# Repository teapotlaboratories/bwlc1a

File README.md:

# blwc1a
 Low-power Cellular GPS Tracker

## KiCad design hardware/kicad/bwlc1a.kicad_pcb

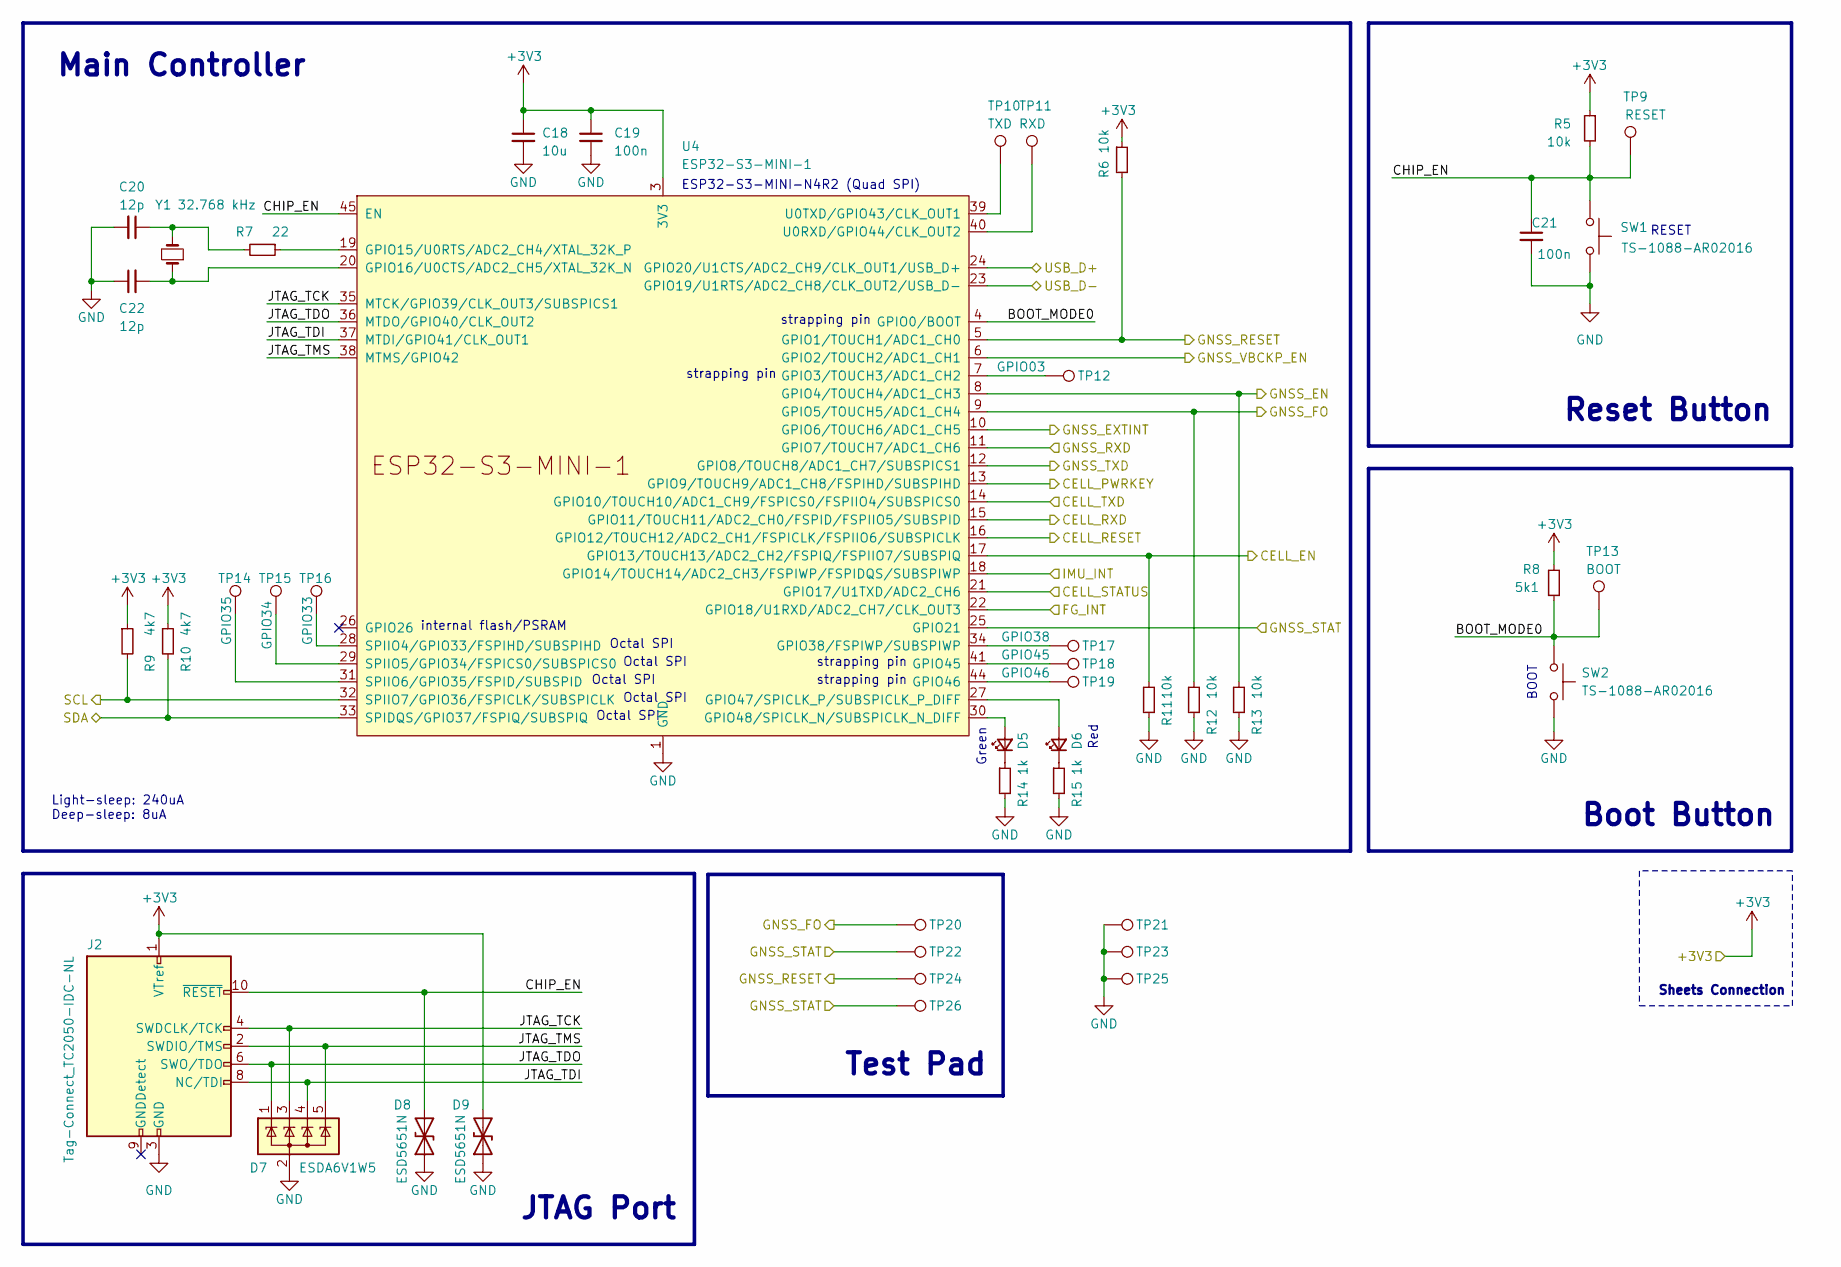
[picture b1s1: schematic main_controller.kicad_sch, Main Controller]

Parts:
C18: 10u; C_0603_1608Metric; Manufacturer Part Number CL10A106KP8NNNC
C19, C21: 100n; C_0402_1005Metric; Manufacturer Part Number CL05B104KO5NNNC
C20, C22: 12p; C_0402_1005Metric; Manufacturer Part Number 0402CG120J500NT
D5: LTST-C191KGKT; LED_0603_1608Metric; Manufacturer Part Number LTST-C191KGKT
D6: LTST-C191KRKT; LED_0603_1608Metric; Manufacturer Part Number LTST-C191KRKT
D7: ESDA6V1W5; SOT-353_SC-70-5; Manufacturer Part Number ESDA6V1W5
D8, D9: ESD5651N; D_SOD-882; Manufacturer Part Number ESD5651N
J2: Tag-Connect_TC2050-IDC-NL; Tag-Connect_TC2050-IDC-NL_2x05_P1.27mm_Vertical
R5, R6, R11, R12, R13: 10k; R_0402_1005Metric; Manufacturer Part Number 0402WGF1002TCE
R7: 22; R_0402_1005Metric; Manufacturer Part Number 0402WGF220JTCE
R8: 5k1; R_0402_1005Metric; Manufacturer Part Number 0402WGF5101TCE
R9, R10: 4k7; R_0402_1005Metric; Manufacturer Part Number 0402WGJ0472TCE
R14, R15: 1k; R_0402_1005Metric; Manufacturer Part Number 0402WGJ0102TCE
SW1, SW2: TS-1088-AR02016; SW-SMD_L3.9-W3.0-P4.45; Manufacturer Part Number TS-1088-AR02016
TP9: RESET; TestPoint_Pad_D1.0mm
TP10: TXD; TestPoint_Pad_D1.0mm
TP11: RXD; TestPoint_Pad_D1.0mm
TP12: GPIO03; TestPoint_Pad_D1.0mm
TP13: BOOT; TestPoint_Pad_D1.0mm
TP14: GPIO35; TestPoint_Pad_D1.0mm
TP15: GPIO34; TestPoint_Pad_D1.0mm
TP16: GPIO33; TestPoint_Pad_D1.0mm
TP17: GPIO38; TestPoint_Pad_D1.0mm
TP18: GPIO45; TestPoint_Pad_D1.0mm
TP19: GPIO46; TestPoint_Pad_D1.0mm
TP20, TP21, TP22, TP23, TP24, TP25, TP26: TestPoint_Pad_D1.0mm
U4: ESP32-S3-MINI-1; Manufacturer Part Number ESP32-S3-MINI-1-N4R2
Y1: 32.768 kHz; Crystal_SMD_3215-2Pin_3.2x1.5mm; Manufacturer Part Number Q13FC1350000400

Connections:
+3V3: C18.1, C19.1, D9.2 (A2), J2.1 (VTref), R5.1, R6.1, R8.2, R9.1, R10.1, U4.3 (3V3); also elsewhere on the board
/Cellular/CELL_PWRKEY: U4.13 (GPIO9/TOUCH9/ADC1_CH8/FSPIHD/SUBSPIHD); also elsewhere on the board
/Cellular/CELL_RESET: U4.16 (GPIO12/TOUCH12/ADC2_CH1/FSPICLK/FSPIIO6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); also elsewhere on the board
/Cellular/CELL_RXD: U4.15 (GPIO11/TOUCH11/ADC2_CH0/FSPID/FSPIIO5/S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); also elsewhere on the board
/Cellular/CELL_STATUS: U4.21 (GPIO17/U1TXD/ADC2_CH6); also elsewhere on the board
/Cellular/CELL_TXD: U4.14 (GPIO10/TOUCH10/ADC1_CH9/FSPICS0/FSPIIO4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); also elsewhere on the board
/GNSS/GNSS_EXTINT: U4.10 (GPIO6/TOUCH6/ADC1_CH5); also elsewhere on the board
/GNSS/GNSS_FO: R12.2, TP20.1, U4.9 (GPIO5/TOUCH5/ADC1_CH4); also elsewhere on the board
/GNSS/GNSS_RESET: R6.2, TP24.1, U4.5 (GPIO1/TOUCH1/ADC1_CH0); also elsewhere on the board
/GNSS/GNSS_RXD: U4.11 (GPIO7/TOUCH7/ADC1_CH6); also elsewhere on the board
/GNSS/GNSS_STAT: TP22.1, TP26.1, U4.25 (GPIO21); also elsewhere on the board
/GNSS/GNSS_TXD: U4.12 (GPIO8/TOUCH8/ADC1_CH7/SUBSPICS1); also elsewhere on the board
/Main Controller/BOOT_MODE0: R8.1, SW2.1, TP13.1, U4.4 (GPIO0/BOOT)
/Main Controller/CELL_EN: R11.2, U4.17 (GPIO13/TOUCH13/ADC2_CH2/FSPIQ/FSPIIO7/S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); also elsewhere on the board
/Main Controller/CHIP_EN: C21.1, D8.2 (A2), J2.10 (~RESET), R5.2, SW1.2, TP9.1, U4.45 (EN)
/Main Controller/FG_INT: U4.22 (GPIO18/U1RXD/ADC2_CH7/CLK_OUT3); also elsewhere on the board
/Main Controller/GNSS_EN: R13.2, U4.8 (GPIO4/TOUCH4/ADC1_CH3); also elsewhere on the board
/Main Controller/GNSS_VBCKP_EN: U4.6 (GPIO2/TOUCH2/ADC1_CH1); also elsewhere on the board
/Main Controller/IMU_INT: U4.18 (GPIO14/TOUCH14/ADC2_CH3/FSPIWP/FSPIDQS/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); also elsewhere on the board
/Main Controller/JTAG_TCK: D7.3 (K), J2.4 (SWDCLK/TCK), U4.35 (MTCK/GPIO39/CLK_OUT3/SUBSPICS1)
/Main Controller/JTAG_TDI: D7.4 (K), J2.8 (NC/TDI), U4.37 (MTDI/GPIO41/CLK_OUT1)
/Main Controller/JTAG_TDO: D7.1 (K), J2.6 (SWO/TDO), U4.36 (MTDO/GPIO40/CLK_OUT2)
/Main Controller/JTAG_TMS: D7.5 (K), J2.2 (SWDIO/TMS), U4.38 (MTMS/GPIO42)
/Main Controller/SCL: R9.2, U4.32 (SPIIO7/GPIO36/FSPICLK/SUBSPICLK); also elsewhere on the board
/Main Controller/SDA: R10.2, U4.33 (SPIDQS/GPIO37/FSPIQ/SUBSPIQ); also elsewhere on the board
/Main Controller/USB_D+: U4.24 (GPIO20/U1CTS/ADC2_CH9/CLK_OUT1/USB_D+); also elsewhere on the board
/Main Controller/USB_D-: U4.23 (GPIO19/U1RTS/ADC2_CH8/CLK_OUT2/USB_D-); also elsewhere on the board
GND: C18.2, C19.2, C20.2, C21.2, C22.1, D7.2 (A), D8.1 (A1), D9.1 (A1), J2.3 (GND), J2.5 (GND), R11.1, R12.1, R13.1, R14.2, R15.2, SW1.1, SW2.2, TP21.1, TP23.1, TP25.1, U4.1 (GND), U4.2 (GND), U4.42 (GND), U4.43 (GND), U4.46 (GND), U4.47 (GND), U4.48 (GND), U4.49 (GND), U4.50 (GND), U4.51 (GND), U4.52 (GND), U4.53 (GND), U4.54 (GND), U4.55 (GND), U4.56 (GND), U4.57 (GND), U4.58 (GND), U4.59 (GND), U4.60 (GND), U4.61 (GND), U4.62 (GND), U4.63 (GND), U4.64 (GND), U4.65 (GND); also elsewhere on the board
unnamed: C20.1, R7.2, Y1.2
unnamed: D5.2 (A), U4.30 (GPIO48/SPICLK_N/SUBSPICLK_N_DIFF)
unnamed: D5.1 (K), R14.1
unnamed: D6.2 (A), U4.27 (GPIO47/SPICLK_P/SUBSPICLK_P_DIFF)
unnamed: D6.1 (K), R15.1
unnamed: TP12.1, U4.7 (GPIO3/TOUCH3/ADC1_CH2)
unnamed: R7.1, U4.19 (GPIO15/U0RTS/ADC2_CH4/XTAL_32K_P)
unnamed: C22.2, U4.20 (GPIO16/U0CTS/ADC2_CH5/XTAL_32K_N), Y1.1
unnamed: TP17.1, U4.34 (GPIO38/FSPIWP/SUBSPIWP)
unnamed: TP18.1, U4.41 (GPIO45)
unnamed: TP19.1, U4.44 (GPIO46)
unnamed: TP16.1, U4.28 (SPIIO4/GPIO33/FSPIHD/SUBSPIHD)
unnamed: TP15.1, U4.29 (SPIIO5/GPIO34/FSPICS0/SUBSPICS0)
unnamed: TP14.1, U4.31 (SPIIO6/GPIO35/FSPID/SUBSPID)
unnamed: TP11.1, U4.40 (U0RXD/GPIO44/CLK_OUT2)
unnamed: TP10.1, U4.39 (U0TXD/GPIO43/CLK_OUT1)

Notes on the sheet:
ESP32-S3-MINI-N4R2 (Quad SPI)
Red
Test Pad
Reset Button
strapping pin
Octal SPI
Main Controller
JTAG Port
Green
Boot Button
RESET
Sheets Connection
internal flash/PSRAM
BOOT
Light-sleep: 240uA Deep-sleep: 8uA

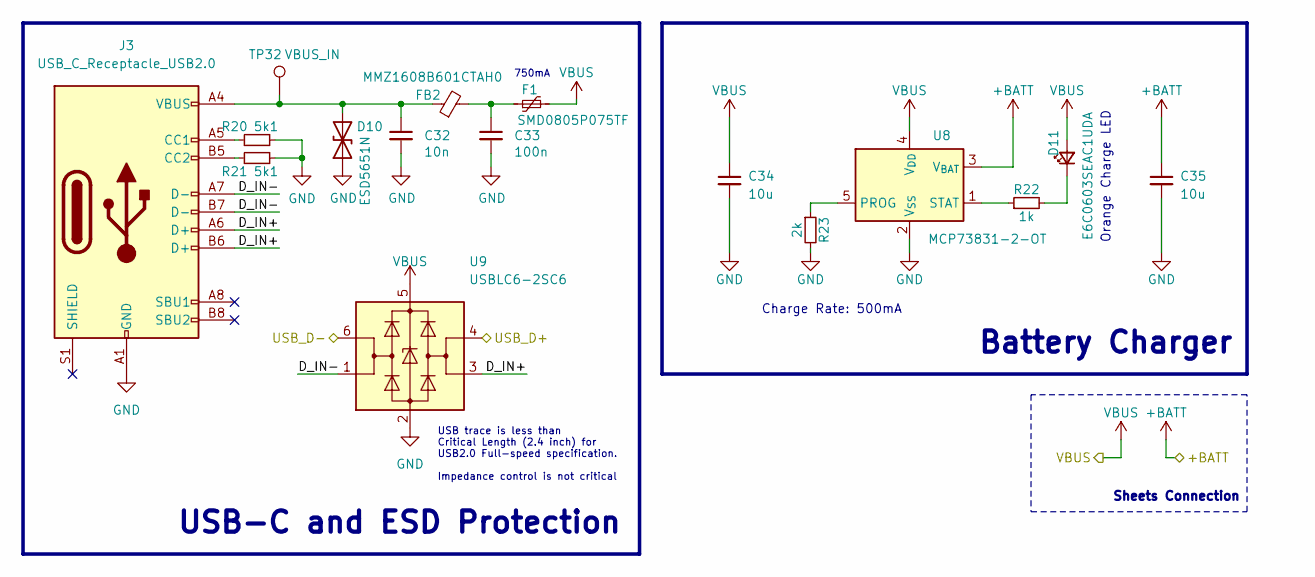
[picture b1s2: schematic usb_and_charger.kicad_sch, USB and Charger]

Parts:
C32: 10n; C_0402_1005Metric; Manufacturer Part Number CC0402KRX7R9BB103
C33: 100n; C_0402_1005Metric; Manufacturer Part Number CL05B104KO5NNNC
C34, C35: 10u; C_0603_1608Metric; Manufacturer Part Number CL10A106KP8NNNC
D10: ESD5651N; D_SOD-882; Manufacturer Part Number ESD5651N
D11: E6C0603SEAC1UDA; LED_0603_1608Metric; Manufacturer Part Number E6C0603SEAC1UDA
F1: SMD0805P075TF; Fuse_0805_2012Metric; Manufacturer Part Number SMD0805P075TF
FB2: MMZ1608B601CTAH0; L_0603_1608Metric; Manufacturer Part Number MMZ1608B601CTAH0
J3: USB_C_Receptacle_USB2.0; USB_C_Receptacle_HRO_TYPE-C-31-M-12; Manufacturer Part Number TYPE-C-31-M-12
R20, R21: 5k1; R_0402_1005Metric; Manufacturer Part Number 0402WGF5101TCE
R22: 1k; R_0402_1005Metric; Manufacturer Part Number 0402WGJ0102TCE
R23: 2k; R_0402_1005Metric; Manufacturer Part Number RC0402FR-072KL
TP32: VBUS_IN; TestPoint_Pad_D1.0mm
U8: MCP73831-2-OT; SOT-23-5; Manufacturer Part Number MCP73831T-2ATI/OT
U9: USBLC6-2SC6; SOT-23-6; Manufacturer Part Number USBLC6-2SC6

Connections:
+BATT: C35.1, U8.3 (V_{BAT}); also elsewhere on the board
/Main Controller/USB_D+: U9.4 (I/O2); also elsewhere on the board
/Main Controller/USB_D-: U9.6 (I/O1); also elsewhere on the board
/USB and Charger/D_IN+: J3.A6 (D+), J3.B6 (D+), U9.3 (I/O2)
/USB and Charger/D_IN-: J3.A7 (D-), J3.B7 (D-), U9.1 (I/O1)
GND: C32.2, C33.2, C34.2, C35.2, D10.1 (A1), J3.A1 (GND), J3.A12 (GND), J3.B1 (GND), J3.B12 (GND), R20.2, R21.2, R23.2, U8.2 (V_{SS}), U9.2 (GND); also elsewhere on the board
unnamed: C33.1, F1.1, FB2.2
unnamed: C32.1, D10.2 (A2), FB2.1, J3.A4 (VBUS), J3.A9 (VBUS), J3.B4 (VBUS), J3.B9 (VBUS), TP32.1
unnamed: D11.1 (K), R22.2
unnamed: J3.A5 (CC1), R20.1
unnamed: J3.B5 (CC2), R21.1
unnamed: R23.1, U8.5 (PROG)
unnamed: R22.1, U8.1 (STAT)
VBUS: C34.1, D11.2 (A), F1.2, U8.4 (V_{DD}), U9.5 (VBUS)

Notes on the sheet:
Orange Charge LED
Battery Charger
USB trace is less than Critical Length (2.4 inch) for USB2.0 Full-speed specification. Impedance control is not critical
Sheets Connection
750mA
Charge Rate: 500mA
USB-C and ESD Protection

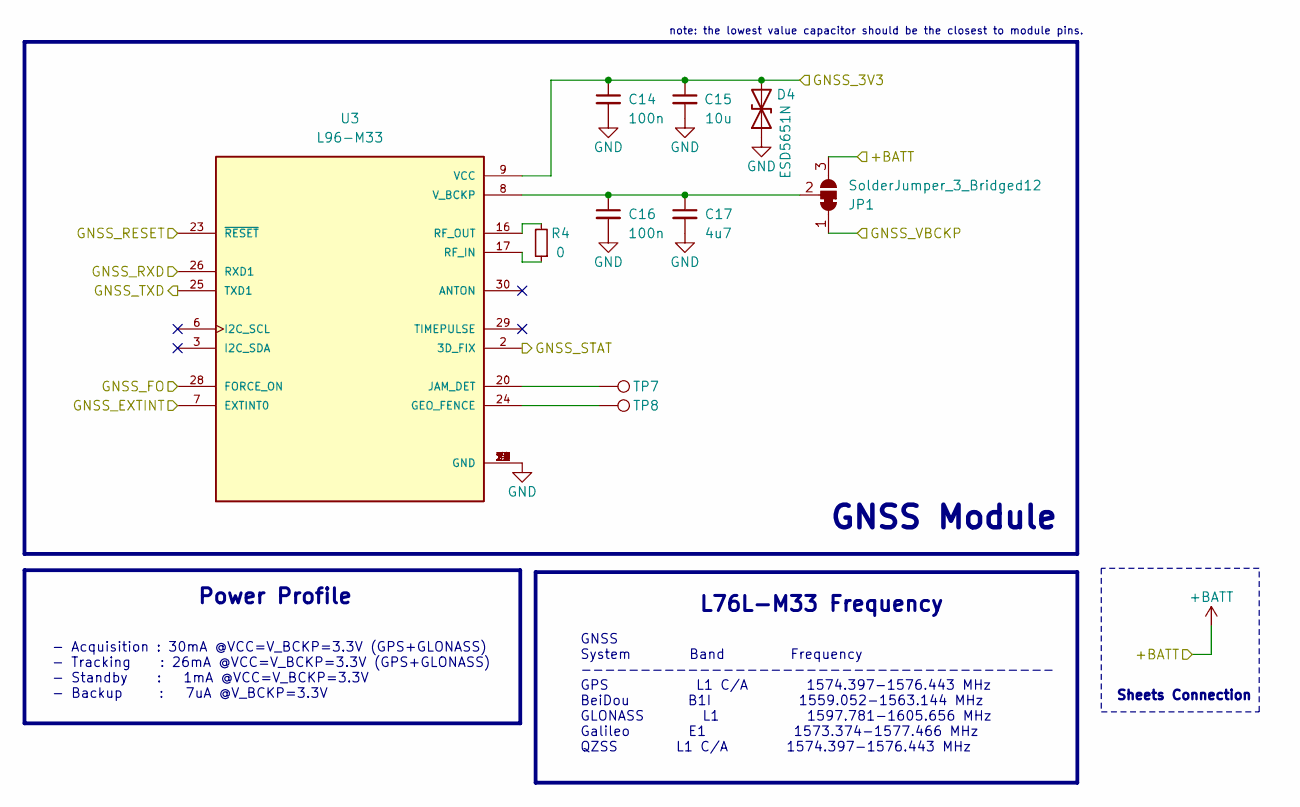
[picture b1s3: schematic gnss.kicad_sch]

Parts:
C14, C16: 100n; C_0402_1005Metric; Manufacturer Part Number CL05B104KO5NNNC
C15: 10u; C_0603_1608Metric; Manufacturer Part Number CL10A106KP8NNNC
C17: 4u7; C_0603_1608Metric; Manufacturer Part Number CL10A475KP8NNNC
D4: ESD5651N; D_SOD-882; Manufacturer Part Number ESD5651N
JP1: SolderJumper_3_Bridged12; SolderJumper-3_P1.3mm_Bridged12_RoundedPad1.0x1.5mm
R4: 0; R_0402_1005Metric; Manufacturer Part Number 0402WGJ0000TCE
TP7, TP8: GPIO46; TestPoint_Pad_D1.0mm
U3: L96-M33; Manufacturer Part Number L96-M33

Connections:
+BATT: JP1.3 (B); also elsewhere on the board
/GNSS/GNSS_EXTINT: U3.7 (EXTINT0); also elsewhere on the board
/GNSS/GNSS_FO: U3.28 (FORCE_ON); also elsewhere on the board
/GNSS/GNSS_RESET: U3.23 (~RESET); also elsewhere on the board
/GNSS/GNSS_RXD: U3.26 (RXD1); also elsewhere on the board
/GNSS/GNSS_STAT: U3.2 (3D_FIX); also elsewhere on the board
/GNSS/GNSS_TXD: U3.25 (TXD1); also elsewhere on the board
/GNSS_3V3: C14.1, C15.1, D4.2 (A2), U3.9 (VCC); also elsewhere on the board
/GNSS_VBCKP: JP1.1 (A); also elsewhere on the board
GND: C14.2, C15.2, C16.2, C17.2, D4.1 (A1), U3.4 (GND), U3.5 (GND), U3.10 (GND), U3.11 (GND), U3.12 (GND), U3.13 (GND), U3.14 (GND), U3.15 (GND), U3.18 (GND), U3.19 (GND), U3.21 (GND), U3.22 (GND), U3.27 (GND), U3.31 (GND); also elsewhere on the board
unnamed: C16.1, C17.1, JP1.2 (C), U3.8 (V_BCKP)
unnamed: TP8.1, U3.24 (GEO_FENCE)
unnamed: TP7.1, U3.20 (JAM_DET)
unnamed: R4.1, U3.17 (RF_IN)
unnamed: R4.2, U3.16 (RF_OUT)

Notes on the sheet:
GNSS Module
- Acquisition : 30mA @VCC=V_BCKP=3.3V (GPS+GLONASS) - Tracking : 26mA @VCC=V_BCKP=3.3V (GPS+GLONASS) - Standby : 1mA @VCC=V_BCKP=3.3V - Backup : 7uA @V_BCKP=3.3V
Sheets Connection
L76L-M33 Frequency
note: the lowest value capacitor should be the closest to module pins.
GNSS System Band Frequency ---------------------------------------- GPS L1 C/A 1574.397-1576.443 MHz BeiDou B1I 1559.052-1563.144 MHz GLONASS L1 1597.781-1605.656 MHz Galileo E1 1573.374-1577.466 MHz QZSS L1 C/A 1574.397-1576.443 MHz
Power Profile

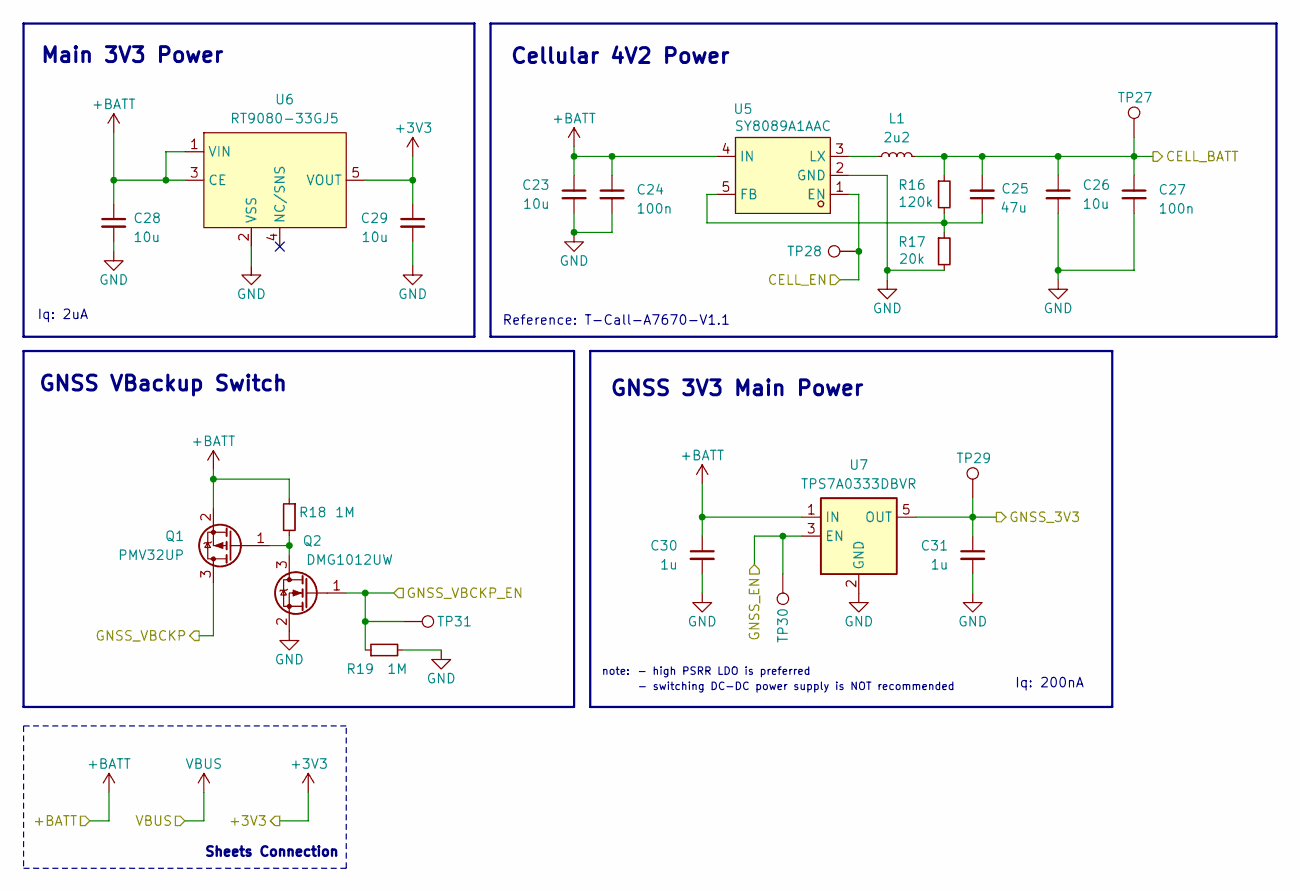
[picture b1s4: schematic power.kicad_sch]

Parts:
C23, C26, C28, C29: 10u; C_0603_1608Metric; Manufacturer Part Number CL10A106KP8NNNC
C24, C27: 100n; C_0603_1608Metric; Manufacturer Part Number CL10B104KO8NNNC
C25: 47u; C_0603_1608Metric; Manufacturer Part Number GRM188R60J476ME15D
C30, C31: 1u; C_0603_1608Metric; Manufacturer Part Number CL10B105KO8NNNC
L1: 2u2; IND-SMD_L3.0-W3.0_LVS303015H-2R2M-N; Manufacturer Part Number LVS303015-2R2M-N
Q1: PMV32UP; SOT-23; Manufacturer Part Number PMV32UP
Q2: DMG1012UW; SOT-323_SC-70; Manufacturer Part Number DMG1012UW-7
R16: 120k; R_0603_1608Metric; Manufacturer Part Number 0603WAF1203T5E
R17: 20k; R_0603_1608Metric; Manufacturer Part Number 0603WAF2002T5E
R18, R19: 1M; R_0603_1608Metric; Manufacturer Part Number 0603WAF1004T5E
TP27, TP28, TP29, TP30, TP31: TestPoint_Pad_D1.0mm
U5: SY8089A1AAC; SOT-23-5; Manufacturer Part Number SY8089A1AAC
U6: RT9080-33GJ5; SOT-23-5; Manufacturer Part Number RT9080-33GJ5
U7: TPS7A0333DBVR; SOT-23-5; Manufacturer Part Number TPS7A0333DBVR

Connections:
+3V3: C29.1, U6.5 (VOUT); also elsewhere on the board
+BATT: C23.1, C24.1, C28.1, C30.1, Q1.2 (S), R18.1, U5.4 (IN), U6.1 (VIN), U6.3 (CE), U7.1 (IN); also elsewhere on the board
/Cellular/CELL_BATT: C25.2, C26.1, C27.1, L1.2, R16.1, TP27.1; also elsewhere on the board
/GNSS_3V3: C31.1, TP29.1, U7.5 (OUT); also elsewhere on the board
/GNSS_VBCKP: Q1.3 (D); also elsewhere on the board
/Main Controller/CELL_EN: TP28.1, U5.1 (EN); also elsewhere on the board
/Main Controller/GNSS_EN: TP30.1, U7.3 (EN); also elsewhere on the board
/Main Controller/GNSS_VBCKP_EN: Q2.1 (G), R19.1, TP31.1; also elsewhere on the board
GND: C23.2, C24.2, C26.2, C27.2, C28.2, C29.2, C30.2, C31.2, Q2.2 (S), R17.2, R19.2, U5.2 (GND), U6.2 (VSS), U7.2 (GND); also elsewhere on the board
unnamed: Q1.1 (G), Q2.3 (D), R18.2
unnamed: C25.1, R16.2, R17.1, U5.5 (FB)
unnamed: L1.1, U5.3 (LX)

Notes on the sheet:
Cellular 4V2 Power
- switching DC-DC power supply is NOT recommended
- high PSRR LDO is preferred
GNSS VBackup Switch
Reference: T-Call-A7670-V1.1
GNSS 3V3 Main Power
Iq: 2uA
Main 3V3 Power
Sheets Connection
note:
Iq: 200nA

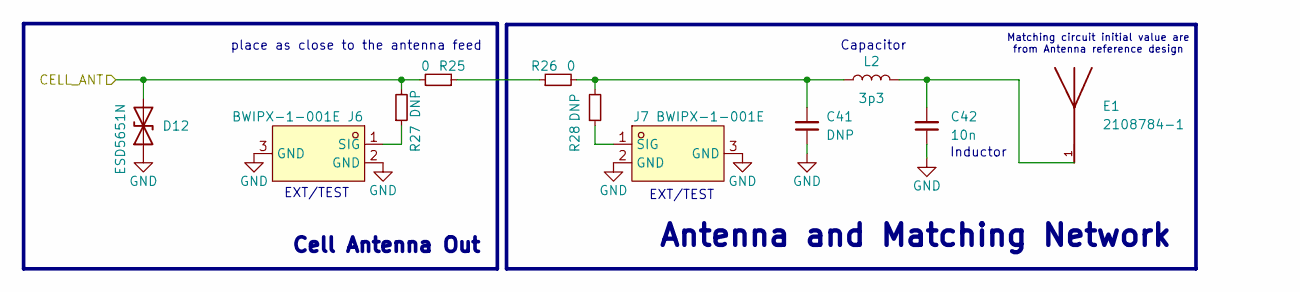
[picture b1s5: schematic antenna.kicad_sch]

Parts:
C41: DNP; C_0402_1005Metric
C42: 10n; C_0402_1005Metric; Manufacturer Part Number LQG15HS10NG02D
D12: ESD5651N; D_SOD-882; Manufacturer Part Number ESD5651N
E1: 2108784-1; Manufacturer Part Number 2108784-1
J6, J7: BWIPX-1-001E; Manufacturer Part Number BWIPX-1-001E
L2: 3p3; L_0402_1005Metric; Manufacturer Part Number GRM1555C1H3R3CA01D
R25, R26: 0; R_0402_1005Metric; Manufacturer Part Number 0402WGJ0000TCE
R27, R28: DNP; R_0402_1005Metric

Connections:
/Antenna/CELL_ANT: D12.2 (A2), R25.2, R27.2; also elsewhere on the board
GND: C41.1, C42.1, D12.1 (A1), J6.2 (GND), J6.3 (GND), J7.2 (GND), J7.3 (GND); also elsewhere on the board
unnamed: C41.2, L2.1, R26.2, R28.2
unnamed: C42.2, E1.1, L2.2
unnamed: J6.1 (SIG), R27.1
unnamed: J7.1 (SIG), R28.1
unnamed: R25.1, R26.1

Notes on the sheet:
Cell Antenna Out
EXT/TEST
Inductor
Antenna and Matching Network
Matching circuit initial value are from Antenna reference design
place as close to the antenna feed
Capacitor

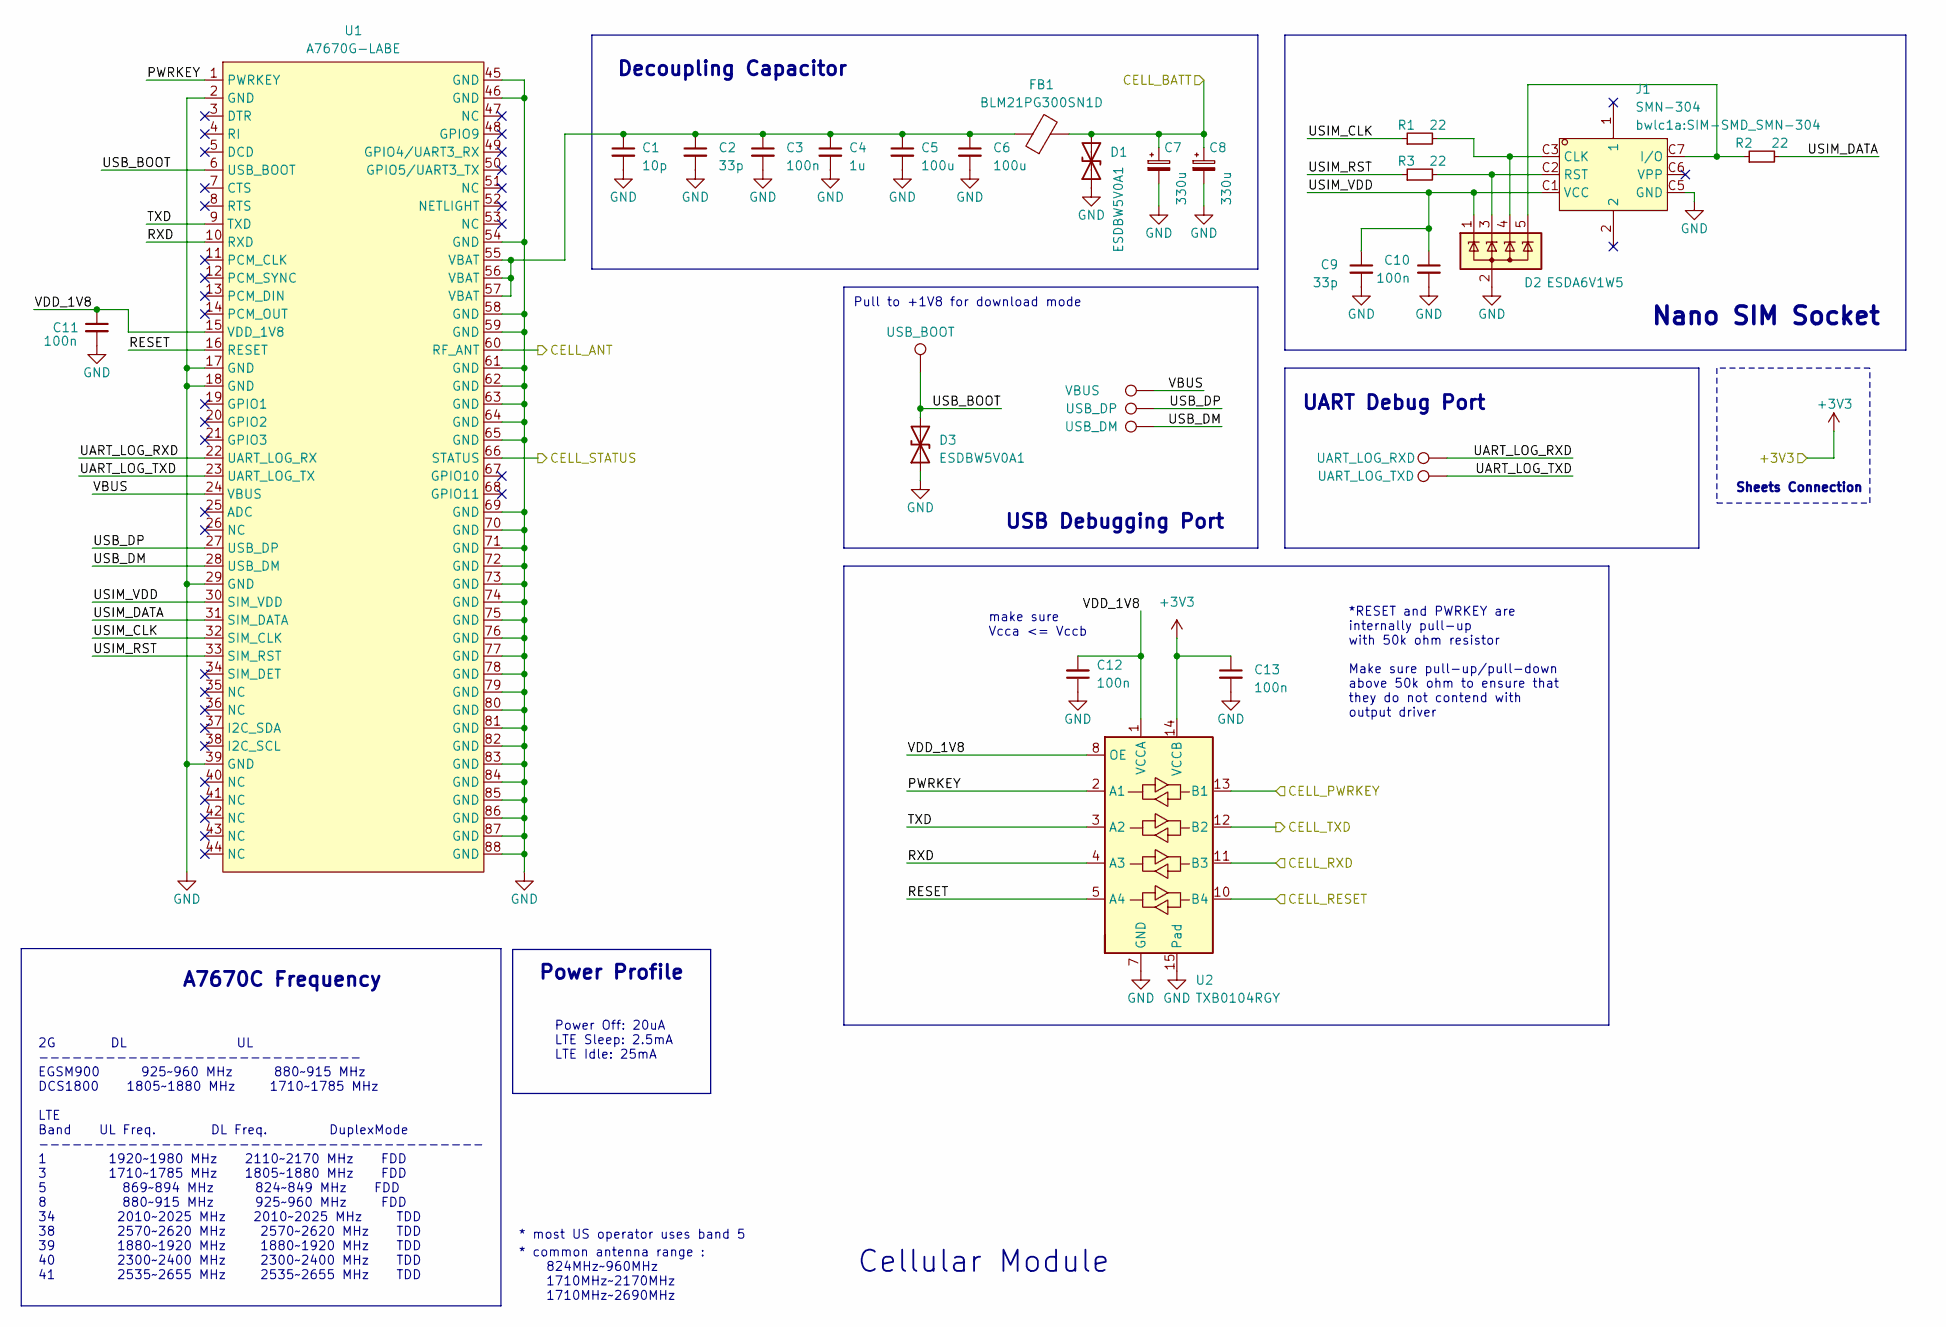
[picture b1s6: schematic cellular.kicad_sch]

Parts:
C1: 10p; C_0402_1005Metric; Manufacturer Part Number CC0402JRNPO9BN100
C2, C9: 33p; C_0402_1005Metric; Manufacturer Part Number 0402CG330J500NT
C3, C10, C11, C12, C13: 100n; C_0402_1005Metric; Manufacturer Part Number CL05B104KO5NNNC
C4: 1u; C_0402_1005Metric; Manufacturer Part Number CL05A105KP5NNNC
C5, C6: 100u; C_0805_2012Metric; Manufacturer Part Number GRM21BR60J107ME15L
C7, C8: 330u; CP_EIA-3528-21_Kemet-B; Manufacturer Part Number T520B337M006ATE040
D1, D3: ESDBW5V0A1; D_SOD-882; Manufacturer Part Number ESDBW5V0A1
D2: ESDA6V1W5; SOT-353_SC-70-5; Manufacturer Part Number ESDA6V1W5
FB1: BLM21PG300SN1D; L_0805_2012Metric; Manufacturer Part Number BLM21PG300SN1D
J1: SMN-304; SIM-SMD_SMN-304; Manufacturer Part Number SMN-304
R1, R2, R3: 22; R_0402_1005Metric; Manufacturer Part Number 0402WGF220JTCE
TP1: USB_BOOT; TestPoint_Pad_D1.0mm
TP2: VBUS; TestPoint_Pad_D1.0mm
TP3: USB_DP; TestPoint_Pad_D1.0mm
TP4: USB_DM; TestPoint_Pad_D1.0mm
TP5: UART_LOG_RXD; TestPoint_Pad_D1.0mm
TP6: UART_LOG_TXD; TestPoint_Pad_D1.0mm
U1: A7670G-LABE; LGA-124_L24.0-W24.0-P1.0-A7670C-LASS; Manufacturer Part Number A7670G-LABE
U2: TXB0104RGY; Texas_S-PVQFN-N14; Manufacturer Part Number TXB0104RGYR

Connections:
+3V3: C13.1, U2.14 (VCCB); also elsewhere on the board
/Antenna/CELL_ANT: U1.60 (RF_ANT); also elsewhere on the board
/Cellular/CELL_BATT: C7.1, C8.1, D1.2 (A2), FB1.2; also elsewhere on the board
/Cellular/CELL_PWRKEY: U2.13 (B1); also elsewhere on the board
/Cellular/CELL_RESET: U2.10 (B4); also elsewhere on the board
/Cellular/CELL_RXD: U2.11 (B3); also elsewhere on the board
/Cellular/CELL_STATUS: U1.66 (STATUS); also elsewhere on the board
/Cellular/CELL_TXD: U2.12 (B2); also elsewhere on the board
/Cellular/PWRKEY: U1.1 (PWRKEY), U2.2 (A1)
/Cellular/RESET: U1.16 (RESET), U2.5 (A4)
/Cellular/RXD: U1.10 (RXD), U2.4 (A3)
/Cellular/TXD: U1.9 (TXD), U2.3 (A2)
/Cellular/UART_LOG_RXD: TP5.1, U1.22 (UART_LOG_RX)
/Cellular/UART_LOG_TXD: TP6.1, U1.23 (UART_LOG_TX)
/Cellular/USB_BOOT: D3.2 (A2), TP1.1, U1.6 (USB_BOOT)
/Cellular/USB_DM: TP4.1, U1.28 (USB_DM)
/Cellular/USB_DP: TP3.1, U1.27 (USB_DP)
/Cellular/USIM_CLK: R1.1, U1.32 (SIM_CLK)
/Cellular/USIM_DATA: R2.2, U1.31 (SIM_DATA)
/Cellular/USIM_RST: R3.1, U1.33 (SIM_RST)
/Cellular/USIM_VDD: C9.1, C10.1, D2.1 (K), J1.C1 (VCC), U1.30 (SIM_VDD)
/Cellular/VBUS: TP2.1, U1.24 (VBUS)
/Cellular/VDD_1V8: C11.1, C12.2, U1.15 (VDD_1V8), U2.1 (VCCA), U2.8 (OE)
GND: C1.2, C2.2, C3.2, C4.2, C5.2, C6.2, C7.2, C8.2, C9.2, C10.2, C11.2, C12.1, C13.2, D1.1 (A1), D2.2 (A), D3.1 (A1), J1.C5 (GND), U1.2 (GND), U1.17 (GND), U1.18 (GND), U1.29 (GND), U1.39 (GND), U1.45 (GND), U1.46 (GND), U1.54 (GND), U1.58 (GND), U1.59 (GND), U1.61 (GND), U1.62 (GND), U1.63 (GND), U1.64 (GND), U1.65 (GND), U1.69 (GND), U1.70 (GND), U1.71 (GND), U1.72 (GND), U1.73 (GND), U1.74 (GND), U1.75 (GND), U1.76 (GND), U1.77 (GND), U1.78 (GND), U1.79 (GND), U1.80 (GND), U1.81 (GND), U1.82 (GND), U1.83 (GND), U1.84 (GND), U1.85 (GND), U1.86 (GND), U1.87 (GND), U1.88 (GND), U2.7 (GND), U2.15 (Pad); also elsewhere on the board
unnamed: C1.1, C2.1, C3.1, C4.1, C5.1, C6.1, FB1.1, U1.55 (VBAT), U1.56 (VBAT), U1.57 (VBAT)
unnamed: D2.4 (K), J1.C3 (CLK), R1.2
unnamed: D2.5 (K), J1.C7 (I/O), R2.1
unnamed: D2.3 (K), J1.C2 (RST), R3.2

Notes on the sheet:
Make sure pull-up/pull-down above 50k ohm to ensure that they do not contend with output driver
Decoupling Capacitor
Pull to +1V8 for download mode
Nano SIM Socket
make sure Vcca <= Vccb
*RESET and PWRKEY are internally pull-up with 50k ohm resistor
Power Off: 20uA LTE Sleep: 2.5mA LTE Idle: 25mA
Sheets Connection
A7670C Frequency
UART Debug Port
2G DL UL ----------------------------- EGSM900 925~960 MHz 880~915 MHz DCS1800 1805~1880 MHz 1710~1785 MHz LTE Band UL Freq. DL Freq. DuplexMode ---------------------------------------- 1 1920~1980 MHz 2110~2170 MHz FDD 3 1710~1785 MHz 1805~1880 MHz FDD 5 869~894 MHz 824~849 MHz FDD 8 880~915 MHz 9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
* most US operator uses band 5
USB Debugging Port
* common antenna range : 824MHz~960MHz 1710MHz~2170MHz 1710MHz~2690MHz
Power Profile
Cellular Module

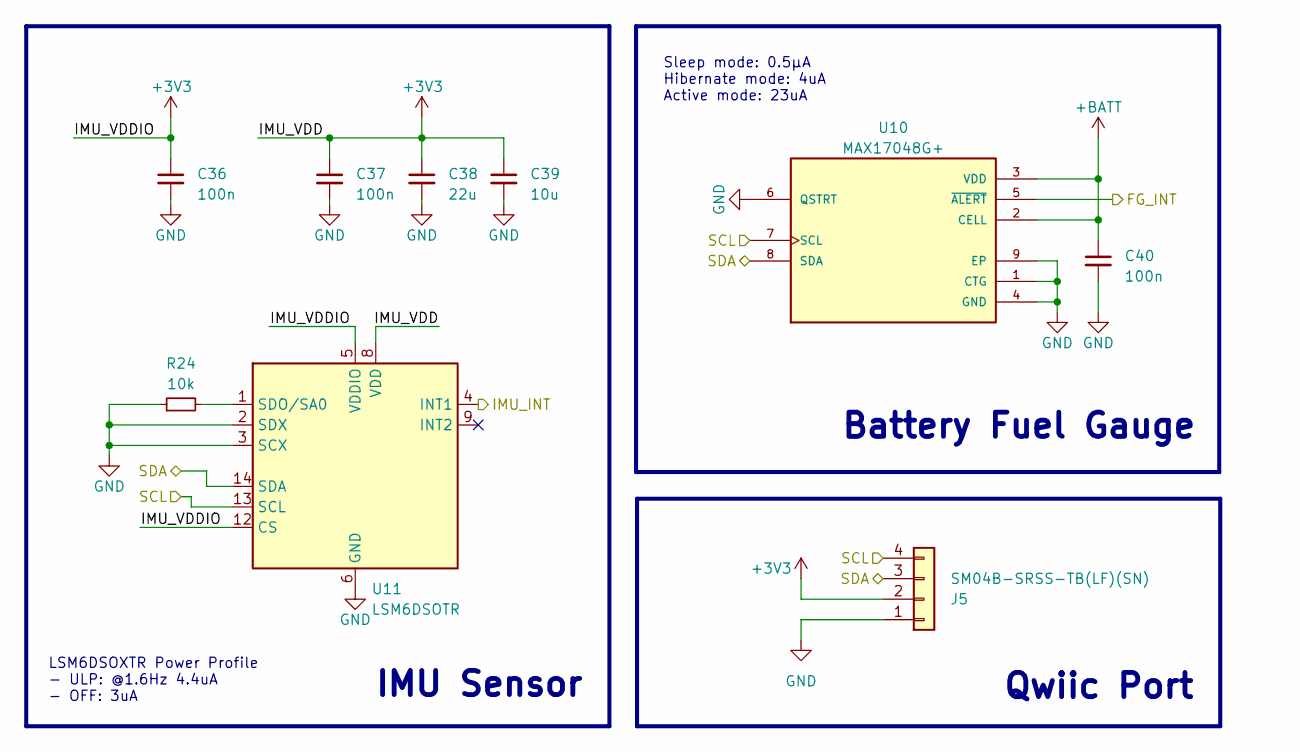
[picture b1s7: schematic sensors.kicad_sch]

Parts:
C36, C37, C40: 100n; C_0402_1005Metric; Manufacturer Part Number CL05B104KO5NNNC
C38: 22u; C_0603_1608Metric; Manufacturer Part Number CL10A226MP8NUNE
C39: 10u; C_0603_1608Metric; Manufacturer Part Number CL10A106KP8NNNC
J5: SM04B-SRSS-TB(LF)(SN); JST_SH_SM04B-SRSS-TB_1x04-1MP_P1.00mm_Horizontal; Manufacturer Part Number SM04B-SRSS-TB(LF)(SN)
R24: 10k; R_0402_1005Metric; Manufacturer Part Number 0402WGF1002TCE
U10: MAX17048G+; DFN-8-1EP_2x2mm_P0.5mm_EP0.7x1.3mm; Manufacturer Part Number MAX17048G+T10
U11: LSM6DSOTR; LGA-14_3x2.5mm_P0.5mm_LayoutBorder3x4y; Manufacturer Part Number LSM6DSOTR

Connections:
+3V3: C36.1, C37.1, C38.1, C39.1, J5.2, U11.5 (VDDIO), U11.8 (VDD), U11.12 (CS); also elsewhere on the board
+BATT: C40.1, U10.2 (CELL), U10.3 (VDD); also elsewhere on the board
/Main Controller/FG_INT: U10.5 (~ALERT); also elsewhere on the board
/Main Controller/IMU_INT: U11.4 (INT1); also elsewhere on the board
/Main Controller/SCL: J5.4, U10.7 (SCL), U11.13 (SCL); also elsewhere on the board
/Main Controller/SDA: J5.3, U10.8 (SDA), U11.14 (SDA); also elsewhere on the board
GND: C36.2, C37.2, C38.2, C39.2, C40.2, J5.1, R24.1, U10.1 (CTG), U10.4 (GND), U10.6 (QSTRT), U10.9 (EP), U11.2 (SDX), U11.3 (SCX), U11.6 (GND), U11.7 (GND); also elsewhere on the board
unnamed: R24.2, U11.1 (SDO/SA0)

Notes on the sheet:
IMU Sensor
LSM6DSOXTR Power Profile - ULP: @1.6Hz 4.4uA - OFF: 3uA
Battery Fuel Gauge
Qwiic Port
Sleep mode: 0.5µA Hibernate mode: 4uA Active mode: 23uA

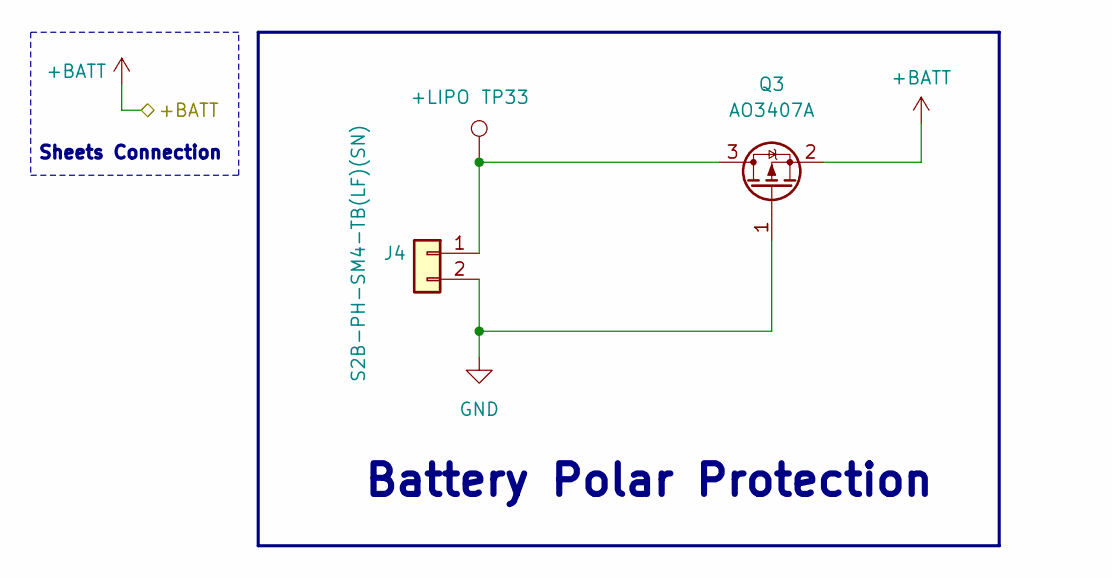
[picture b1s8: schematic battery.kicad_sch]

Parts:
J4: S2B-PH-SM4-TB(LF)(SN); JST_PH_S2B-PH-SM4-TB_1x02-1MP_P2.00mm_Horizontal; Manufacturer Part Number S2B-PH-SM4-TB(LF)(SN)
Q3: AO3407A; SOT-23; Part Description MOSFET P Channel 30V 4.3A 48mΩ@10V,4.3A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
TP33: +LIPO; TestPoint_Pad_D1.0mm

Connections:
+BATT: Q3.2 (S); also elsewhere on the board
GND: J4.2, Q3.1 (G); also elsewhere on the board
unnamed: J4.1, Q3.3 (D), TP33.1

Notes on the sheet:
Battery Polar Protection
Sheets Connection
